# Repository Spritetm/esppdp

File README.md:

#What is this?

This is the source repository for esppdp, which is a tiny VT-102 scale model housing an
ESP32 emulating a PDP11. You can connect a BlueTooth keyboard to it and play the
original Tetris, or do some die-hard computing on 2.11BSD.

#Why?

Well, someone had to put back the 'mini' in 'minicomputer', right?

---

This fork contains a set of patches to correct build errors in IDF 5.0
Ian Schofield (Isysxp)
October 2023

---

This fork integrates the sunton ESP32 2832S028 board. I try to do this in a way it simplifys the integration of other boards.
Patched for IDF 5.2.1

SvenMb
April 2024

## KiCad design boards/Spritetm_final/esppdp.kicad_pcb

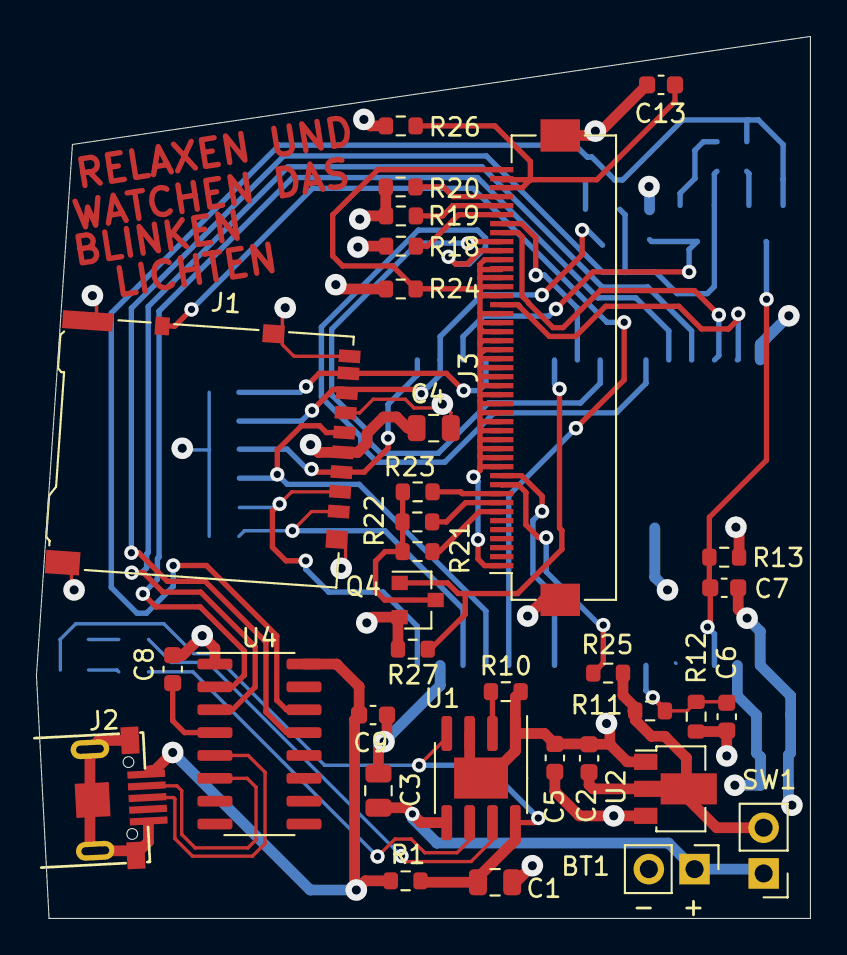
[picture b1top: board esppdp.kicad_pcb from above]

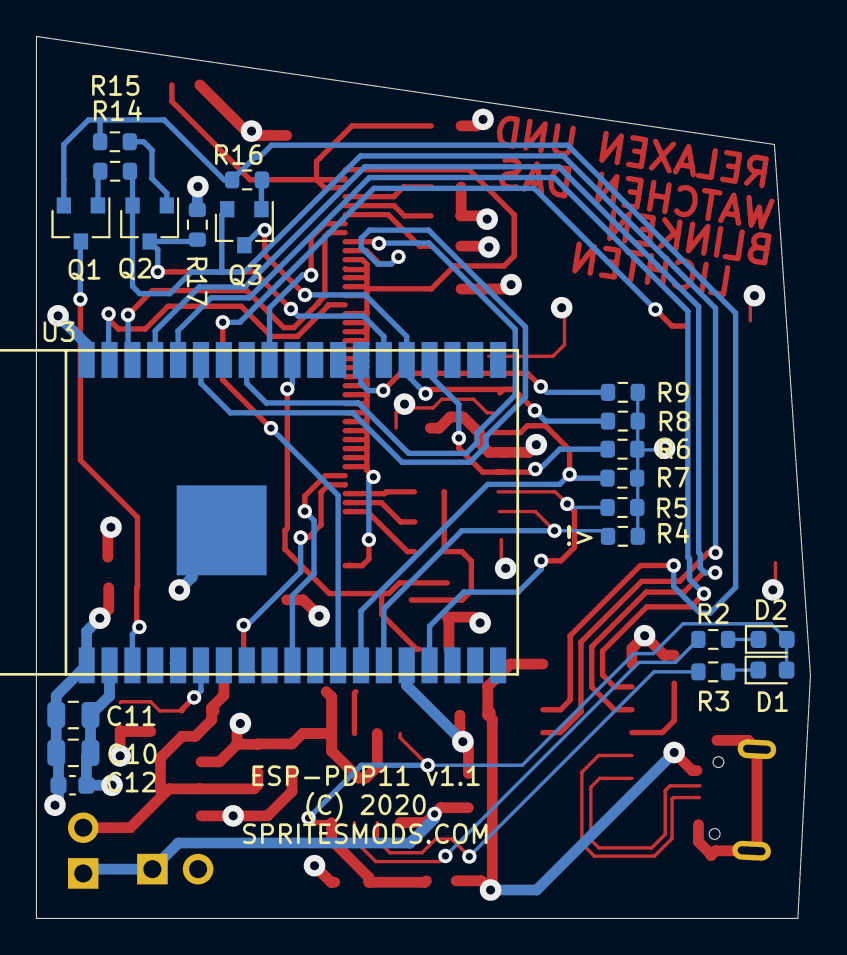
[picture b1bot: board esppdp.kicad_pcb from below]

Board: 4 copper layers, 43.0 x 49.0 mm, 55 parts (21 on the bottom side), 48 nets.

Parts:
BT1: Battery_Cell; PinHeader_1x02_P2.54mm_Vertical
C1, C3, C4, C10, C11: 10u; C_0805_2012Metric
C2: 1u; C_0603_1608Metric
C5: 2.2u; C_0603_1608Metric
C6, C7, C8, C9, C12, C13: 100n; C_0603_1608Metric
D1: GREEN; LED_0603_1608Metric
D2: RED; LED_0603_1608Metric
J1: Micro_SD_Card_Det_Hirose_DM3AT; microSD_HC_Hirose_DM3AT-SF-PEJM5
J2: USB_B_Micro; USB_Micro-B_China_MK5P
J3: LCD_KD018QVFMN010; Hirose_FH12-45S-0.5SH_1x45-1MP_P0.50mm_Horizontal_Descendin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
Q1, Q2, Q3: S8050; SOT-23
Q4: AO3400A; SOT-23
R1: 0.4R; R_0603_1608Metric
R2, R3: 1K; R_0603_1608Metric
R4, R5, R6, R7, R8, R9, R13, R17, R27: 10K; R_0603_1608Metric
R10: 4K; R_0603_1608Metric
R11, R14, R15, R16: 100K; R_0603_1608Metric
R12: 33K; R_0603_1608Metric
R18, R19, R20, R24, R25, R26: 0; R_0603_1608Metric
R21, R22, R23: 50; R_0603_1608Metric
SW1: SW_SPST; PinHeader_1x02_P2.54mm_Vertical
U1: TP4056; SOIC-8-1EP_3.9x4.9mm_P1.27mm_EP2.29x3mm
U2: HT7833_SOT89; SOT-89-3
U3: ESP-WROVER32; ESP-WROVER-MOD
U4: CH340C; SOIC-16_3.9x9.9mm_P1.27mm

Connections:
/EN: C7.1, Q1.3, R13.2, U3.3
/ESP_RXD: U3.34, U4.2
/ESP_TXD: U3.35, U4.3
/IO0: Q2.3, R17.2, U3.25
/LCD_BL: Q4.1, R27.1, U3.29
/LCD_CS: J3.8, U3.36
/LCD_MISO: J3.35, U3.10
/LCD_MOSI: J3.16, U3.37
/LCD_RESET: J3.7, U3.30
/LCD_RS: J3.10, U3.33
/LCD_SCL: J3.9, U3.31
/SD_CLK: J1.5, R7.2, U3.13
/SD_CMD: J1.3, R6.2, U3.23
/SD_D0: J1.7, Q3.3, R8.2, U3.24
/SD_D1: J1.8, R9.2, U3.26
/SD_D2: J1.1, R4.2, U3.14
/SD_D3: J1.2, R5.2, U3.16
/SD_DET: J1.10, U3.12
/USB_5V: C9.1, J2.1, R1.1, U4.16
/VBAT: C2.1, R11.1, R25.1, SW1.2, U2.2
GND: BT1.2, C1.2, C2.2, C3.2, C4.2, C5.2, C6.2, C7.2, C8.2, C9.2, C10.2, C11.2, C12.2, C13.2, J1.6, J1.9, J1.11, J2.5, J2.6, J3.MP, Q4.2, R10.2, R12.2, R18.1, R24.1, R27.2, U1.1, U1.3, U1.9, U2.1, U3.1, U3.15, U3.38, U3.39, U4.1
unnamed: BT1.1, C3.1, SW1.1, U1.5
unnamed: C1.1, D1.2, D2.2, R1.2, U1.4, U1.8
unnamed: C6.1, R11.2, R12.1, U3.6
unnamed: C8.1, U4.4
unnamed: C13.1, J3.2, J3.3, R26.1
unnamed: D1.1, R3.2
unnamed: D2.1, R2.2
unnamed: J2.2, U4.6
unnamed: J2.3, U4.5
unnamed: J3.1, J3.11, J3.12, J3.13, J3.14, J3.15, J3.17, J3.18, J3.19, J3.20, J3.21, J3.22, J3.23, J3.24, J3.25, J3.26, J3.27, J3.28, J3.29, J3.30, J3.31, J3.32, J3.33, J3.34, J3.45, R24.2
unnamed: J3.4, R20.2
unnamed: J3.5, R19.2
unnamed: J3.6, R18.2
unnamed: J3.36, R25.2
unnamed: J3.37, R23.1
unnamed: J3.38, R22.1
unnamed: J3.39, R21.1
unnamed: Q1.1, R14.1
unnamed: Q1.2, R15.2, R16.2, U4.14
unnamed: Q2.1, R15.1
unnamed: Q2.2, Q3.2, R14.2, U4.13
unnamed: Q3.1, R16.1
unnamed: Q4.3, R21.2, R22.2, R23.2
unnamed: R2.1, U1.7
unnamed: R3.1, U1.6
unnamed: R10.1, U1.2
VCC: C4.1, C5.1, C10.1, C11.1, C12.1, J1.4, R4.1, R5.1, R6.1, R7.1, R8.1, R9.1, R13.1, R17.1, R19.1, R20.1, R26.2, U2.3, U3.2

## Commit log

2020-08-28 Initial, non-compiling, attempt
2020-08-28 Fixes, crlf
2020-08-29 Hackhack... compiles but does not link now
2020-08-29 Add host build stuff
2020-08-29 Simplified the crap out of the disk routines, they work now
2020-08-29 Preparing to slay the scp beast....
2020-08-30 Lots of hacking but it works. Now to move it to the ESP32...
2020-09-04 Compiles for esp32; yay!
2020-09-05 32K saved and it still works!
2020-09-27 Tweaks?
2020-09-29 Tetris works, BTHID does its thing, now to fix BSD2.11...
2020-09-29 Make BSD2.11 work
2020-10-18 Add WiFi
2020-10-22 Shared LWIP/PDP11 IP stack thing works, fix BT to work with WiFi as well
2020-10-22 Save some memory by breaking pdp11 register debugging...
2020-10-23 Add BT keyboard support
2020-10-23 Numkeys
2020-11-14 Copying some non-display improvements from 240x240 branch
2020-11-27 Add wifid support
2020-11-29 Make wifid connect/reconnect work
2020-12-17 Clean up some printfs, try to set freertos ticks lower
2021-01-01 Auto-detect hard disk image to boot into BSD or Tetris
2021-01-11 Add pcb, wifid etc to same git repo, clean up
2021-01-11 Add copyright stuff
2021-01-11 Add readme
2021-01-12 Do not hang when no AP is found; fix devkit/final hw selection; fix openscad typo
2021-01-15 pcb label move to make moar readable
2021-01-20 Correct typo in model file
    Correct doubled paren in openscad
2021-01-20 update to remove lcd place holder

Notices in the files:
boards/Spritetm_final/esppdp.kicad_pcb:
(C) 2020
